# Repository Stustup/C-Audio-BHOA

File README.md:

# Balanced Headphone Operational Amplifier

A high powered differential headphone amp with a focus on modularity and prototyping. Inspired by the Schiit Audio Magni Heresy.

## Features

- All sections of the amp should be modular (Filter, VA, CA, Output protection)
- All sections should be accessable via pin headers
- Output power >1W per channel

## Schematic

The Amp consists of a simple differential input filter for very high frequency noise, an instrumential amplifier input stage for differential voltage amplification and 8 paralelled opamp sections in buffer topology per channel (of which there are 4 for differential amplification for a total of 16 opamps(!!!). [Mental, I know](http://www.diyaudio.com/archive/blogs/alexcp/attachments/1049d1368388175-ne5532-power-amplifier-ne553205.jpg)). 

The instrumental amplifier in the prestage was chosen, because it is really easy and straight forward to set the gain with just a a single resistor per channel.

Furthermore the output is protected via muting relays driven by a mosfet and a turn on timer for a startup delay. 

The power supply is off board to stay in the limits of JLCPCBs cheap 100x100mm PCB service. It can range from +-5V to +-18V (or how much the Opamps will take). The output relays are 5V, a simple 78l05 so8 IC is supplying them with 5V. 

## TODO

- Improve stability of current amplification. Maybe high value resistors to ground to give a reference for the inputs. Also cascaded topology might be a better CA stage as per [SBOA553A](https://www.ti.com/lit/ab/sboa553a/sboa553a.pdf?ts=1741260128432)
- Improve output protection. Firstly ADD some DC protection and improve the circuit for setting delay time.

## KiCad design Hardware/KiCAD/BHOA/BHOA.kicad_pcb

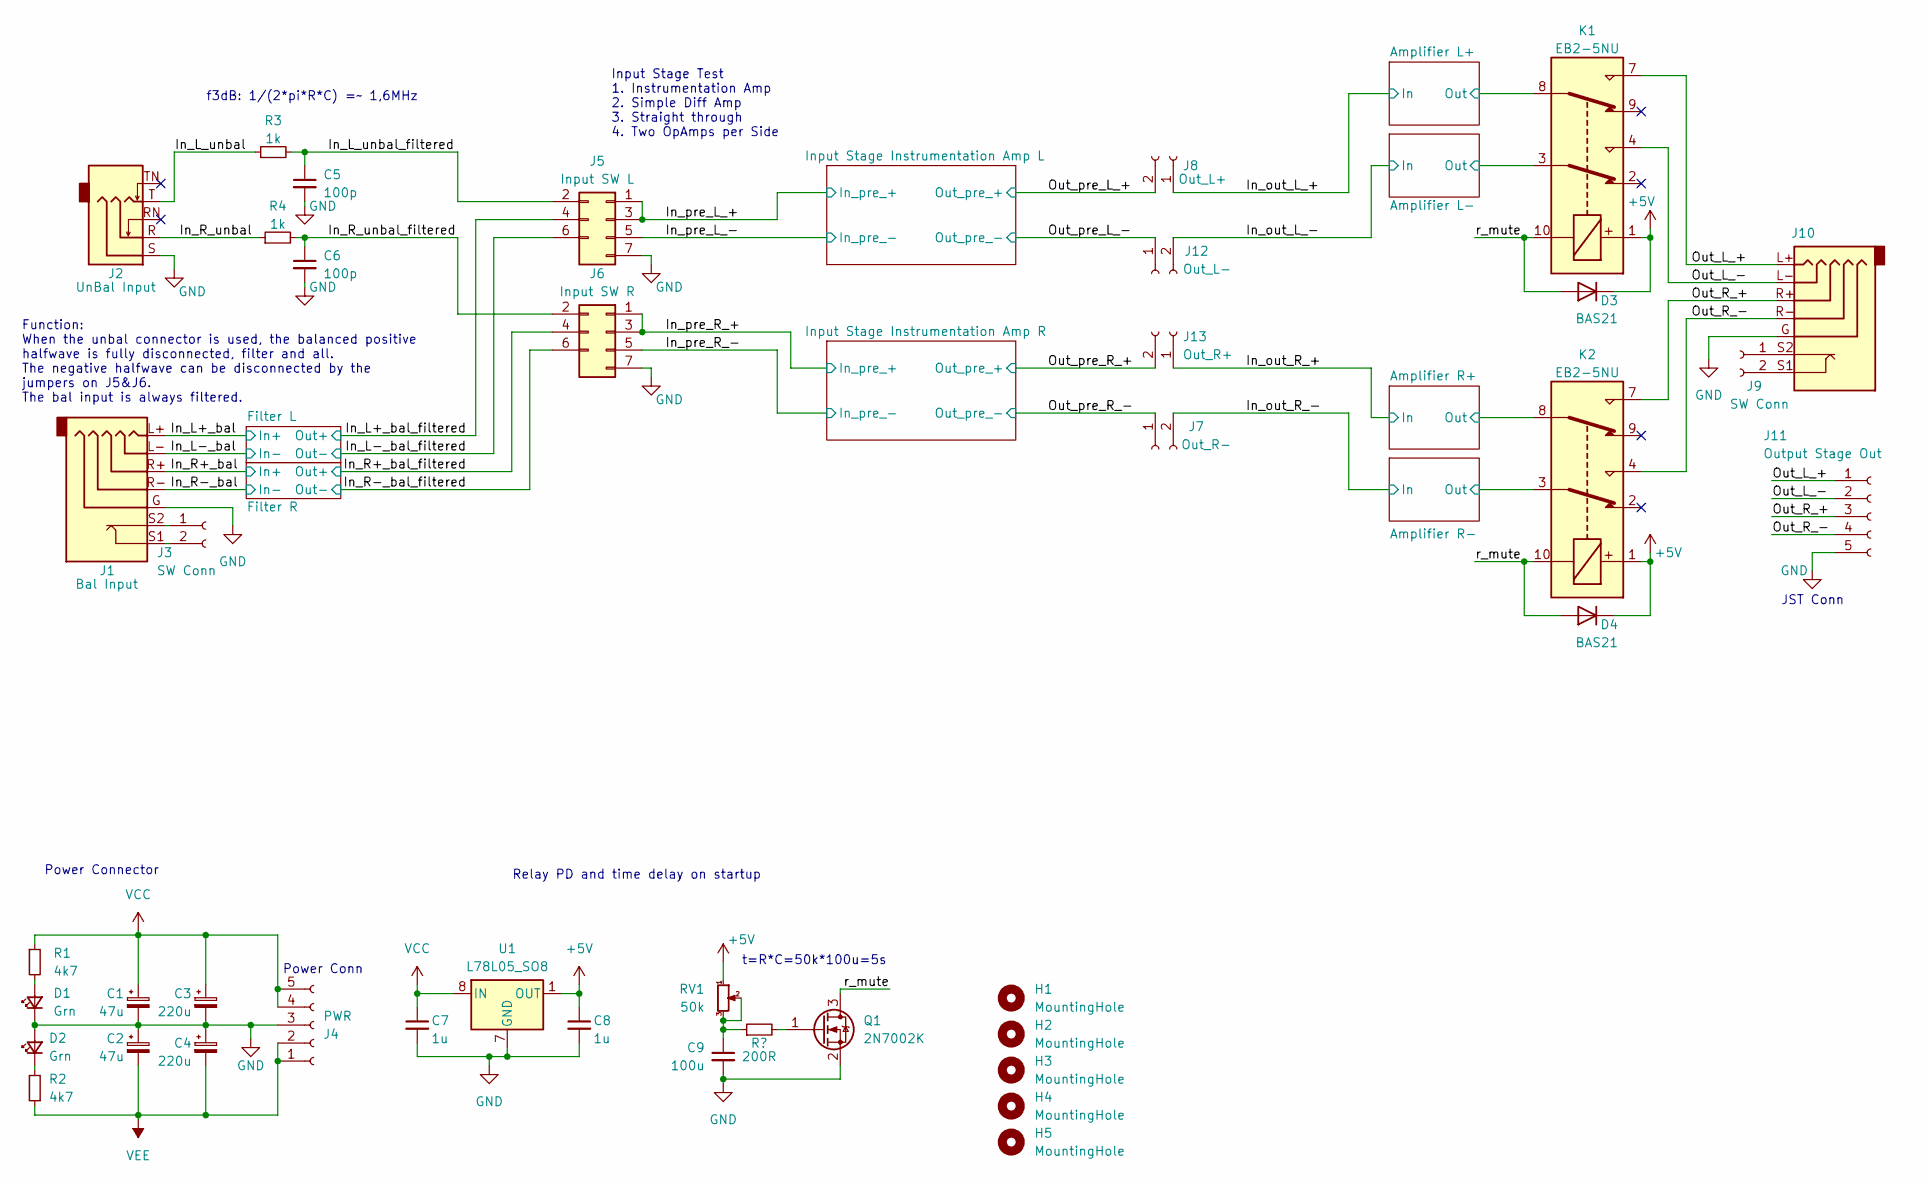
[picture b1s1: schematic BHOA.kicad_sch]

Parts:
C1, C2: 47u; CP_Elec_6.3x5.8; Mouser 140-VZL470M1VTR-0606
C3, C4: 220u; CP_Elec_8x10
C5, C6: 100p; C_0805_2012Metric_Pad1.18x1.45mm_HandSolder
C7, C8: 1u; C_0805_2012Metric_Pad1.18x1.45mm_HandSolder
C9: 100u; R_0805_2012Metric_Pad1.20x1.40mm_HandSolder; Mouser 187-CL31A107MPKNNWE
D1, D2: Grn; LED_0805_2012Metric_Pad1.15x1.40mm_HandSolder
D3, D4: BAS21; SOT-23; Mouser 78-BAS21-HE3-18
H1, H2, H3, H4, H5: MountingHole; MountingHole_3.7mm
J1: Bal Input; Pentaconn
J2: UnBal Input; Jack_3.5mm_Ledino_KB3SPRS_Horizontal
J3, J9: SW Conn; PinHeader_1x02_P2.54mm_Vertical
J4: PWR; JST_EH_B5B-EH-A_1x05_P2.50mm_Vertical
J5: Input SW L; PinHeader_2x04_P2.54mm_Vertical
J6: Input SW R; PinHeader_2x04_P2.54mm_Vertical
J7: Out_R-; PinHeader_1x02_P2.54mm_Vertical
J8: Out_L+; PinHeader_1x02_P2.54mm_Vertical
J10: Pentaconn
J11: Output Stage Out; PinSocket_1x05_P2.54mm_Vertical
J12: Out_L-; PinHeader_1x02_P2.54mm_Vertical
J13: Out_R+; PinHeader_1x02_P2.54mm_Vertical
K1, K2: EB2-5NU; Relay_DPDT_FRT5_SMD
Q1: 2N7002K; SOT-23
R1, R2: 4k7; R_0805_2012Metric_Pad1.20x1.40mm_HandSolder
R3, R4: 1k; R_0805_2012Metric_Pad1.20x1.40mm_HandSolder
R5: 200R; R_0805_2012Metric_Pad1.20x1.40mm_HandSolder
RV1: 50k; Potentiometer_Bourns_TC33X_Vertical; Mouser 652-TC33X-2-503G
U1: L78L05_SO8; SOIC-8_3.9x4.9mm_P1.27mm

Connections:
+5V: C8.1, D3.3 (K), D4.3 (K), K1.1, K2.1, RV1.1, U1.1 (OUT)
/Amplifier L+/Out: K1.8; also elsewhere on the board
/Amplifier L-/Out: K1.3; also elsewhere on the board
/Amplifier R+/Out: K2.8; also elsewhere on the board
/Amplifier R-/Out: K2.3; also elsewhere on the board
/In_L+_bal: J1.L+; also elsewhere on the board
/In_L+_bal_filtered: J5.4; also elsewhere on the board
/In_L-_bal: J1.L-; also elsewhere on the board
/In_L-_bal_filtered: J5.6; also elsewhere on the board
/In_L_unbal: J2.T, R3.1
/In_L_unbal_filtered: C5.1, J5.2, R3.2
/In_R+_bal: J1.R+; also elsewhere on the board
/In_R+_bal_filtered: J6.4; also elsewhere on the board
/In_R-_bal: J1.R-; also elsewhere on the board
/In_R-_bal_filtered: J6.6; also elsewhere on the board
/In_R_unbal: J2.R, R4.1
/In_R_unbal_filtered: C6.1, J6.2, R4.2
/In_out_L_+: J8.1; also elsewhere on the board
/In_out_L_-: J12.2; also elsewhere on the board
/In_out_R_+: J13.1; also elsewhere on the board
/In_out_R_-: J7.2; also elsewhere on the board
/In_pre_L_+: J5.1, J5.3; also elsewhere on the board
/In_pre_L_-: J5.5; also elsewhere on the board
/In_pre_R_+: J6.1, J6.3; also elsewhere on the board
/In_pre_R_-: J6.5; also elsewhere on the board
/Out_L_+: J10.L+, J11.1, K1.7
/Out_L_-: J10.L-, J11.2, K1.4
/Out_R_+: J10.R+, J11.3, K2.7
/Out_R_-: J10.R-, J11.4, K2.4
/Out_pre_L_+: J8.2; also elsewhere on the board
/Out_pre_L_-: J12.1; also elsewhere on the board
/Out_pre_R_+: J13.2; also elsewhere on the board
/Out_pre_R_-: J7.1; also elsewhere on the board
/r_mute: D3.1 (A), D4.1 (A), K1.10, K2.10, Q1.3 (D)
GND: C1.2, C2.1, C3.2, C4.1, C5.2, C6.2, C7.2, C8.2, C9.2, D1.1 (K), D2.2 (A), J1.G, J2.S, J4.3, J5.7, J6.7, J10.G, J11.5, Q1.2 (S), U1.2 (GND), U1.3 (GND), U1.6 (GND), U1.7 (GND); also elsewhere on the board
unnamed: C9.1, R5.1, RV1.2, RV1.3
unnamed: D1.2 (A), R1.2
unnamed: D2.1 (K), R2.2
unnamed: J1.S2, J3.1
unnamed: J1.S1, J3.2
unnamed: J9.1, J10.S2
unnamed: J9.2, J10.S1
unnamed: Q1.1 (G), R5.2
VCC: C1.1, C3.1, C7.1, J4.4, J4.5, R1.1, U1.8 (IN); also elsewhere on the board
VEE: C2.2, C4.2, J4.1, J4.2, R2.1; also elsewhere on the board

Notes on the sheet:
JST Conn
t=R*C=50k*100u=5s
Relay PD and time delay on startup
Power Connector
Power Conn
Function: When the unbal connector is used, the balanced positive halfwave is fully disconnected, filter and all. The negative halfwave can be disconnected by the jumpers on J5&J6. The bal input is always filtered.
f3dB: 1/(2*pi*R*C) =~ 1,6MHz
Input Stage Test 1. Instrumentation Amp 2. Simple Diff Amp 3. Straight through 4. Two OpAmps per Side

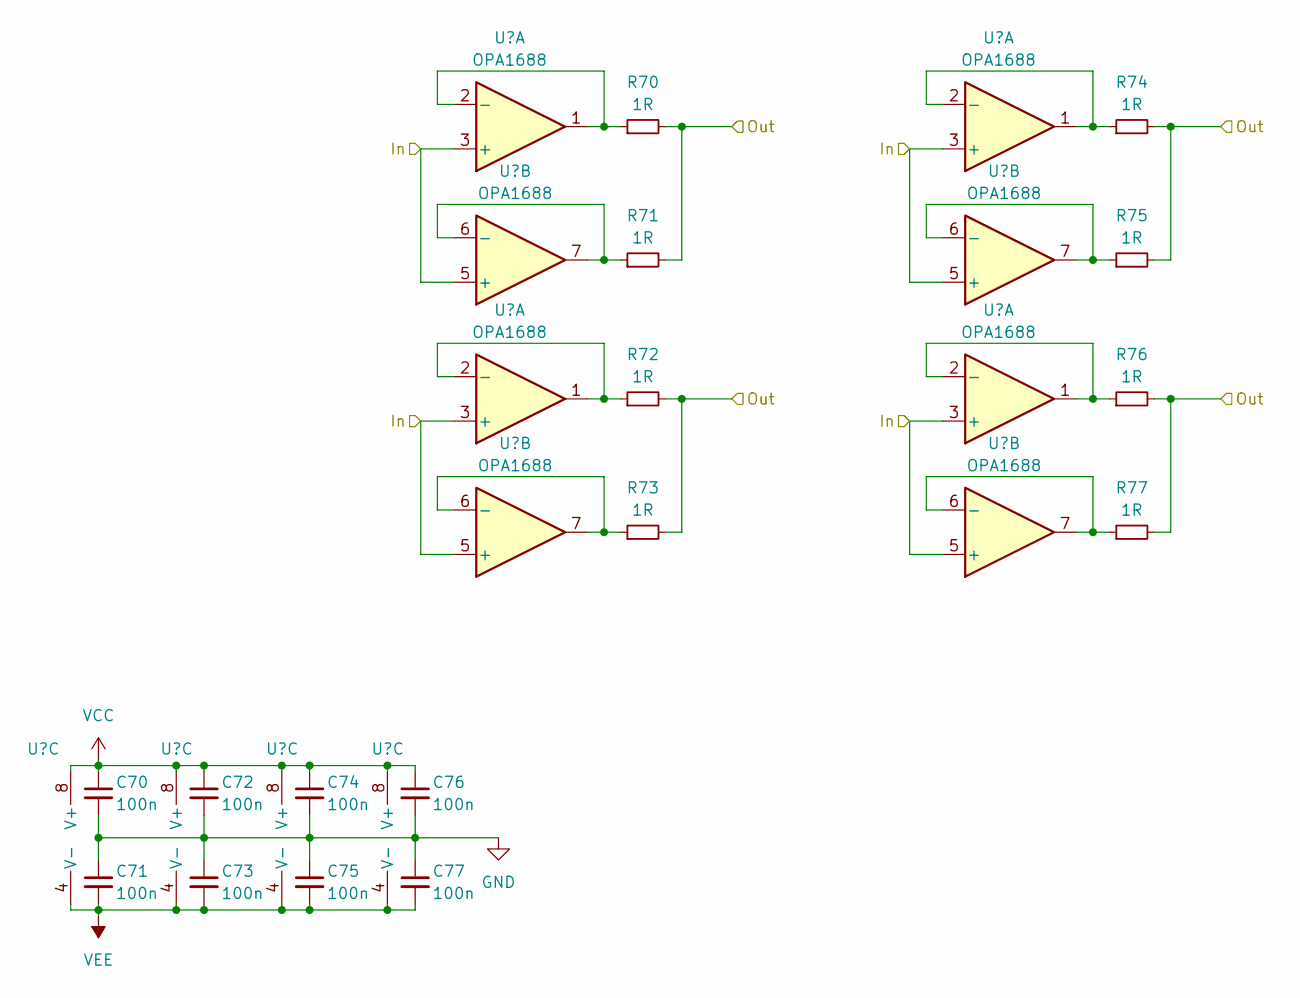
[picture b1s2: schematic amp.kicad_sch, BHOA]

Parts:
C70, C71, C72, C73, C74, C75, C76, C77: 100n; C_0805_2012Metric_Pad1.18x1.45mm_HandSolder
R70, R71, R72, R73, R74, R75, R76, R77: 1R; R_1206_3216Metric_Pad1.30x1.75mm_HandSolder
U70, U71, U72, U73: OPA1688; SOIC-8_3.9x4.9mm_P1.27mm

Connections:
/Amplifier L-/Out: R70.2, R71.2, R72.2, R73.2, R74.2, R75.2, R76.2, R77.2; also elsewhere on the board
/In_out_L_-: U70.3 (+), U70.5 (+), U71.3 (+), U71.5 (+), U72.3 (+), U72.5 (+), U73.3 (+), U73.5 (+); also elsewhere on the board
GND: C70.2, C71.1, C72.2, C73.1, C74.2, C75.1, C76.2, C77.1; also elsewhere on the board
unnamed: R70.1, U70.1, U70.2 (-)
unnamed: R71.1, U70.6 (-), U70.7
unnamed: R72.1, U71.1, U71.2 (-)
unnamed: R73.1, U71.6 (-), U71.7
unnamed: R74.1, U72.1, U72.2 (-)
unnamed: R75.1, U72.6 (-), U72.7
unnamed: R76.1, U73.1, U73.2 (-)
unnamed: R77.1, U73.6 (-), U73.7
VCC: C70.1, C72.1, C74.1, C76.1, U70.8 (V+), U71.8 (V+), U72.8 (V+), U73.8 (V+); also elsewhere on the board
VEE: C71.2, C73.2, C75.2, C77.2, U70.4 (V-), U71.4 (V-), U72.4 (V-), U73.4 (V-); also elsewhere on the board

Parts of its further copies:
C60, C61, C62, C63, C64, C65, C66, C67, C80, C81, C82, C83, C84, C85, C86, C87, C90, C91, C92, C93, C94, C95, C96, C97: 100n; C_0805_2012Metric_Pad1.18x1.45mm_HandSolder
R60, R61, R62, R63, R64, R65, R66, R67, R80, R81, R82, R83, R84, R85, R86, R87, R90, R91, R92, R93, R94, R95, R96, R97: 1R; R_1206_3216Metric_Pad1.30x1.75mm_HandSolder
U60, U61, U62, U63, U80, U81, U82, U83, U90, U91, U92, U93: OPA1688; SOIC-8_3.9x4.9mm_P1.27mm

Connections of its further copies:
/Amplifier L+/Out: R60.2, R61.2, R62.2, R63.2, R64.2, R65.2, R66.2, R67.2; also elsewhere on the board
/Amplifier R+/Out: R80.2, R81.2, R82.2, R83.2, R84.2, R85.2, R86.2, R87.2; also elsewhere on the board
/Amplifier R-/Out: R90.2, R91.2, R92.2, R93.2, R94.2, R95.2, R96.2, R97.2; also elsewhere on the board
/In_out_L_+: U60.3 (+), U60.5 (+), U61.3 (+), U61.5 (+), U62.3 (+), U62.5 (+), U63.3 (+), U63.5 (+); also elsewhere on the board
/In_out_R_+: U80.3 (+), U80.5 (+), U81.3 (+), U81.5 (+), U82.3 (+), U82.5 (+), U83.3 (+), U83.5 (+); also elsewhere on the board
/In_out_R_-: U90.3 (+), U90.5 (+), U91.3 (+), U91.5 (+), U92.3 (+), U92.5 (+), U93.3 (+), U93.5 (+); also elsewhere on the board
GND: C60.2, C61.1, C62.2, C63.1, C64.2, C65.1, C66.2, C67.1, C80.2, C81.1, C82.2, C83.1, C84.2, C85.1, C86.2, C87.1, C90.2, C91.1, C92.2, C93.1, C94.2, C95.1, C96.2, C97.1; also elsewhere on the board
unnamed: R60.1, U60.1, U60.2 (-)
unnamed: R61.1, U60.6 (-), U60.7
unnamed: R62.1, U61.1, U61.2 (-)
unnamed: R63.1, U61.6 (-), U61.7
unnamed: R64.1, U62.1, U62.2 (-)
unnamed: R65.1, U62.6 (-), U62.7
unnamed: R66.1, U63.1, U63.2 (-)
unnamed: R67.1, U63.6 (-), U63.7
unnamed: R80.1, U80.1, U80.2 (-)
unnamed: R81.1, U80.6 (-), U80.7
unnamed: R82.1, U81.1, U81.2 (-)
unnamed: R83.1, U81.6 (-), U81.7
unnamed: R84.1, U82.1, U82.2 (-)
unnamed: R85.1, U82.6 (-), U82.7
unnamed: R86.1, U83.1, U83.2 (-)
unnamed: R87.1, U83.6 (-), U83.7
unnamed: R90.1, U90.1, U90.2 (-)
unnamed: R91.1, U90.6 (-), U90.7
unnamed: R92.1, U91.1, U91.2 (-)
unnamed: R93.1, U91.6 (-), U91.7
unnamed: R94.1, U92.1, U92.2 (-)
unnamed: R95.1, U92.6 (-), U92.7
unnamed: R96.1, U93.1, U93.2 (-)
unnamed: R97.1, U93.6 (-), U93.7
VCC: C60.1, C62.1, C64.1, C66.1, C80.1, C82.1, C84.1, C86.1, C90.1, C92.1, C94.1, C96.1, U60.8 (V+), U61.8 (V+), U62.8 (V+), U63.8 (V+), U80.8 (V+), U81.8 (V+), U82.8 (V+), U83.8 (V+), U90.8 (V+), U91.8 (V+), U92.8 (V+), U93.8 (V+); also elsewhere on the board
VEE: C61.2, C63.2, C65.2, C67.2, C81.2, C83.2, C85.2, C87.2, C91.2, C93.2, C95.2, C97.2, U60.4 (V-), U61.4 (V-), U62.4 (V-), U63.4 (V-), U80.4 (V-), U81.4 (V-), U82.4 (V-), U83.4 (V-), U90.4 (V-), U91.4 (V-), U92.4 (V-), U93.4 (V-); also elsewhere on the board

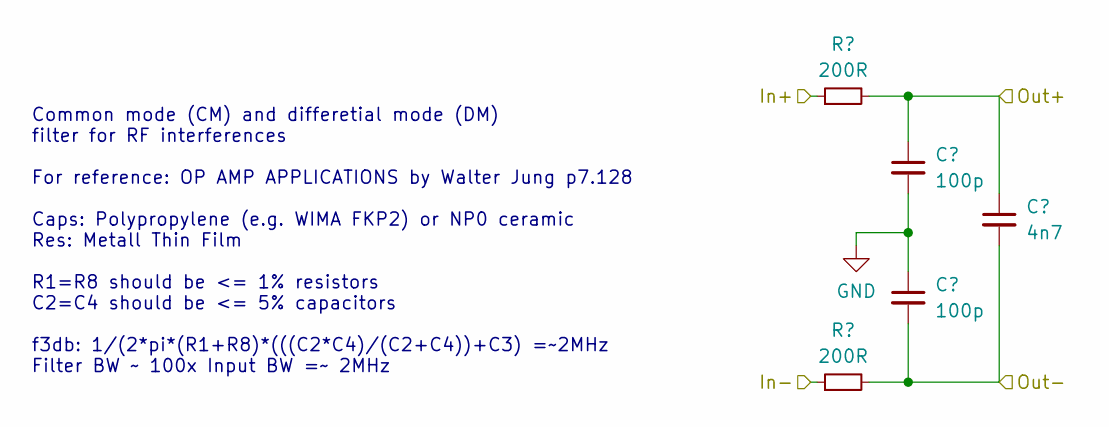
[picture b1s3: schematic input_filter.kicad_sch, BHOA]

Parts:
C20, C21: 100p; C_0805_2012Metric_Pad1.18x1.45mm_HandSolder
C22: 4n7; C_0805_2012Metric_Pad1.18x1.45mm_HandSolder
R20, R21: 200R; R_0805_2012Metric_Pad1.20x1.40mm_HandSolder

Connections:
/In_L+_bal: R20.1; also elsewhere on the board
/In_L+_bal_filtered: C20.1, C22.1, R20.2; also elsewhere on the board
/In_L-_bal: R21.1; also elsewhere on the board
/In_L-_bal_filtered: C21.2, C22.2, R21.2; also elsewhere on the board
GND: C20.2, C21.1; also elsewhere on the board

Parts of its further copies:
C30, C31: 100p; C_0805_2012Metric_Pad1.18x1.45mm_HandSolder
C32: 4n7; C_0805_2012Metric_Pad1.18x1.45mm_HandSolder
R30, R31: 200R; R_0805_2012Metric_Pad1.20x1.40mm_HandSolder

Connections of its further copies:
/In_R+_bal: R30.1; also elsewhere on the board
/In_R+_bal_filtered: C30.1, C32.1, R30.2; also elsewhere on the board
/In_R-_bal: R31.1; also elsewhere on the board
/In_R-_bal_filtered: C31.2, C32.2, R31.2; also elsewhere on the board
GND: C30.2, C31.1; also elsewhere on the board

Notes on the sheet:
Common mode (CM) and differetial mode (DM) filter for RF interferences For reference: OP AMP APPLICATIONS by Walter Jung p7.128 Caps: Polypropylene (e.g. WIMA FKP2) or NP0 ceramic Res: Metall Thin Film R1=R8 should be <= 1% resistors C2=C4 should be <= 5% capacitors f3db: 1/(2*pi*(R1+R8)*(((C2*C4)/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

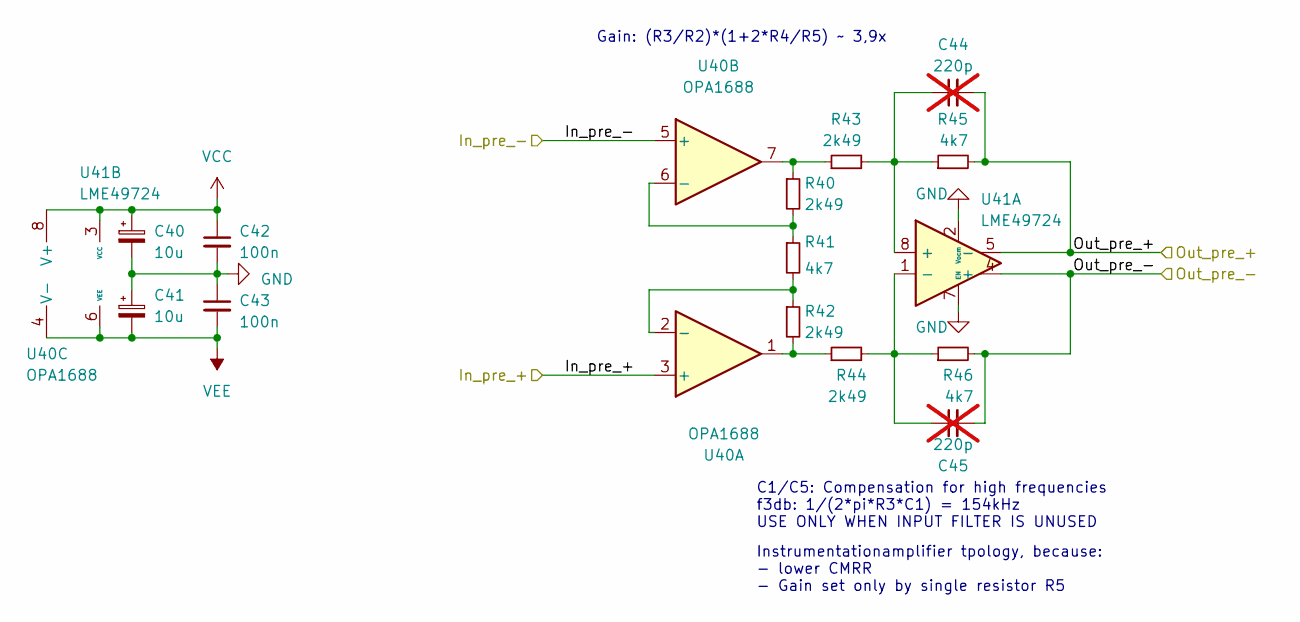
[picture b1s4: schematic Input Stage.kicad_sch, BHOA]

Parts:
C40, C41: 10u; C_1206_3216Metric_Pad1.33x1.80mm_HandSolder
C42, C43: 100n; C_0805_2012Metric_Pad1.18x1.45mm_HandSolder
C44, C45: 220p; C_0805_2012Metric_Pad1.18x1.45mm_HandSolder; not fitted
R40, R42, R43, R44: 2k49; R_0805_2012Metric_Pad1.20x1.40mm_HandSolder
R41: 4k7; R_1206_3216Metric_Pad1.30x1.75mm_HandSolder
R45, R46: 4k7; R_0805_2012Metric_Pad1.20x1.40mm_HandSolder
U40: OPA1688; SOIC-8_3.9x4.9mm_P1.27mm
U41: LME49724; SOIC-8_3.9x4.9mm_P1.27mm

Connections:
/In_pre_L_+: U40.3 (+); also elsewhere on the board
/In_pre_L_-: U40.5 (+); also elsewhere on the board
/Out_pre_L_+: C44.2, R45.2, U41.5 (-); also elsewhere on the board
/Out_pre_L_-: C45.2, R46.2, U41.4 (+); also elsewhere on the board
GND: C40.2, C41.1, C42.2, C43.1, U41.2 (Vocm), U41.7 (EN); also elsewhere on the board
unnamed: C44.1, R43.2, R45.1, U41.8 (+)
unnamed: C45.1, R44.2, R46.1, U41.1 (-)
unnamed: R40.1, R43.1, U40.7
unnamed: R42.2, R44.1, U40.1
unnamed: R41.2, R42.1, U40.2 (-)
unnamed: R40.2, R41.1, U40.6 (-)
VCC: C40.1, C42.1, U40.8 (V+), U41.3 (VCC); also elsewhere on the board
VEE: C41.2, C43.2, U40.4 (V-), U41.6 (VEE); also elsewhere on the board

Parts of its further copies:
C50, C51: 10u; C_1206_3216Metric_Pad1.33x1.80mm_HandSolder
C52, C53: 100n; C_0805_2012Metric_Pad1.18x1.45mm_HandSolder
C54, C55: 220p; C_0805_2012Metric_Pad1.18x1.45mm_HandSolder; not fitted
R50, R52, R53, R54: 2k49; R_0805_2012Metric_Pad1.20x1.40mm_HandSolder
R51: 4k7; R_1206_3216Metric_Pad1.30x1.75mm_HandSolder
R55, R56: 4k7; R_0805_2012Metric_Pad1.20x1.40mm_HandSolder
U50: OPA1688; SOIC-8_3.9x4.9mm_P1.27mm
U51: LME49724; SOIC-8_3.9x4.9mm_P1.27mm

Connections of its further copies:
/In_pre_R_+: U50.3 (+); also elsewhere on the board
/In_pre_R_-: U50.5 (+); also elsewhere on the board
/Out_pre_R_+: C54.2, R55.2, U51.5 (-); also elsewhere on the board
/Out_pre_R_-: C55.2, R56.2, U51.4 (+); also elsewhere on the board
GND: C50.2, C51.1, C52.2, C53.1, U51.2 (Vocm), U51.7 (EN); also elsewhere on the board
unnamed: C54.1, R53.2, R55.1, U51.8 (+)
unnamed: C55.1, R54.2, R56.1, U51.1 (-)
unnamed: R50.1, R53.1, U50.7
unnamed: R52.2, R54.1, U50.1
unnamed: R51.2, R52.1, U50.2 (-)
unnamed: R50.2, R51.1, U50.6 (-)
VCC: C50.1, C52.1, U50.8 (V+), U51.3 (VCC); also elsewhere on the board
VEE: C51.2, C53.2, U50.4 (V-), U51.6 (VEE); also elsewhere on the board

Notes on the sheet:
C1/C5: Compensation for high frequencies f3db: 1/(2*pi*R3*C1) = 154kHz USE ONLY WHEN INPUT FILTER IS UNUSED
Instrumentationamplifier tpology, because: - lower CMRR - Gain set only by single resistor R5
Gain: (R3/R2)*(1+2*R4/R5) ~ 3,9x

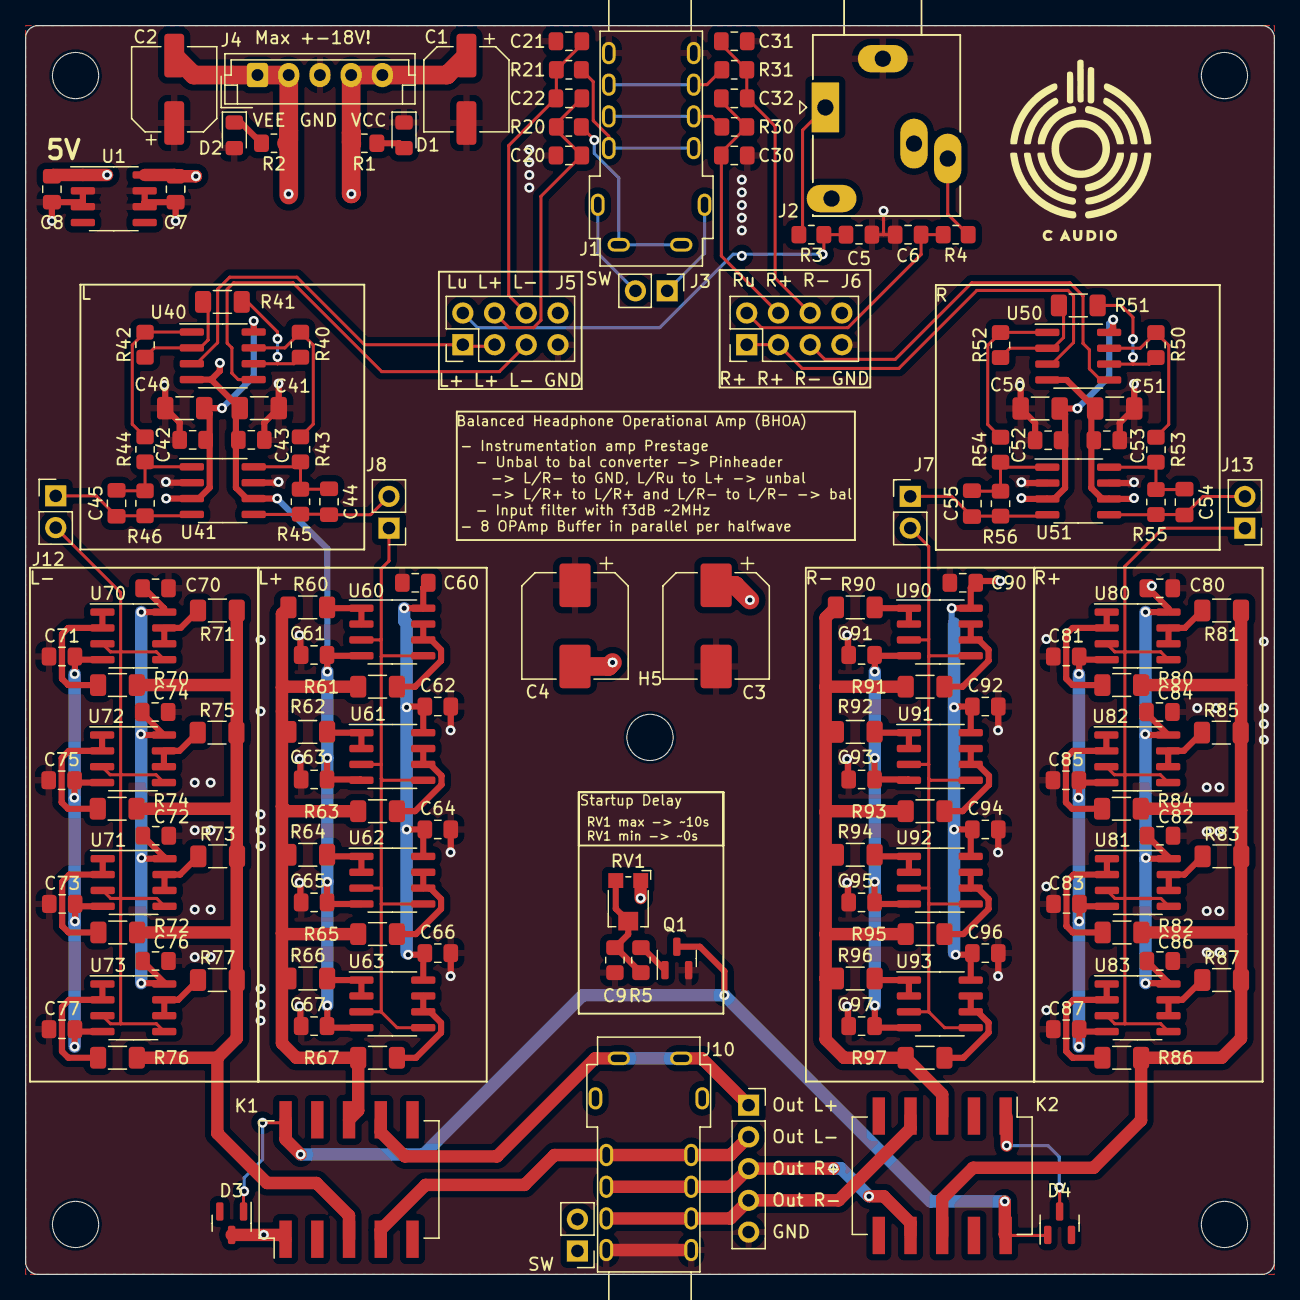
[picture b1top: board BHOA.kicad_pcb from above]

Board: 4 copper layers, 100.0 x 100.0 mm, 161 parts (0 on the bottom side), 89 nets.

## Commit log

2024-01-17 Update README.md
    added readme
2024-01-17 added the project
2024-01-17 changed logo to c audio
2024-01-17 added outpout relays
2024-01-18 Updated PCB with output protection
2024-01-18 housekeeping
2025-03-06 Added Pics and PDF
2025-03-06 added schematic pic
2025-03-06 added schematic to readme
2025-03-06 added psu notice to readme
2025-03-06 added
2025-03-19 modified readme
2025-03-19 Create LICENSE
